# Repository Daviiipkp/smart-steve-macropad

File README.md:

# Smart Steve Commander v1

A custom mechanical macropad designed to control the "Smart Steve" personal automation assistant. It features a rotary encoder for volume/media control, an OLED screen for system status, and 8 mechanical keys for shortcuts.

Designed using KiCad and Fusion 360.

## Features
* **MCU:** Seeed XIAO RP2040
* **Inputs:** 8x MX-Style Mechanical Switches + 1x EC11 Rotary Encoder
* **Display:** 0.91" OLED I2C Display
* **Lighting:** 1x SK6812 (Neopixel) RGB LED for status indication
* **Case:** 3D Printed Sandwich Case

## Project Structure
* `/CAD`: Contains the complete 3D assembly (.STEP)
* `/PCB`: KiCad source files
* `/Firmware`: CircuitPython/KMK placeholder

## Bill of Materials (BOM)

| Component | Quantity | Description |
| :--- | :--- | :--- |
| Seeed XIAO RP2040 | 1 | Microcontroller |
| Cherry MX Style Switch | 8 | Mechanical Keys |
| Keycaps | 8 | 1U Keycaps |
| EC11 Rotary Encoder | 1 | Encoder with Push Button |
| 0.91" OLED Display | 1 | I2C 128x32 Display |
| SK6812 / WS2812B | 1 | RGB LED (5050 package) |
| 1N4148 Diodes | 9 | Through-hole diodes |
| 3D Printed Case | 1 | PLA/PETG |

## Gallery

### 3D Assembly

### PCB Layout

### Schematic

### Case Assembly (Cross Section)

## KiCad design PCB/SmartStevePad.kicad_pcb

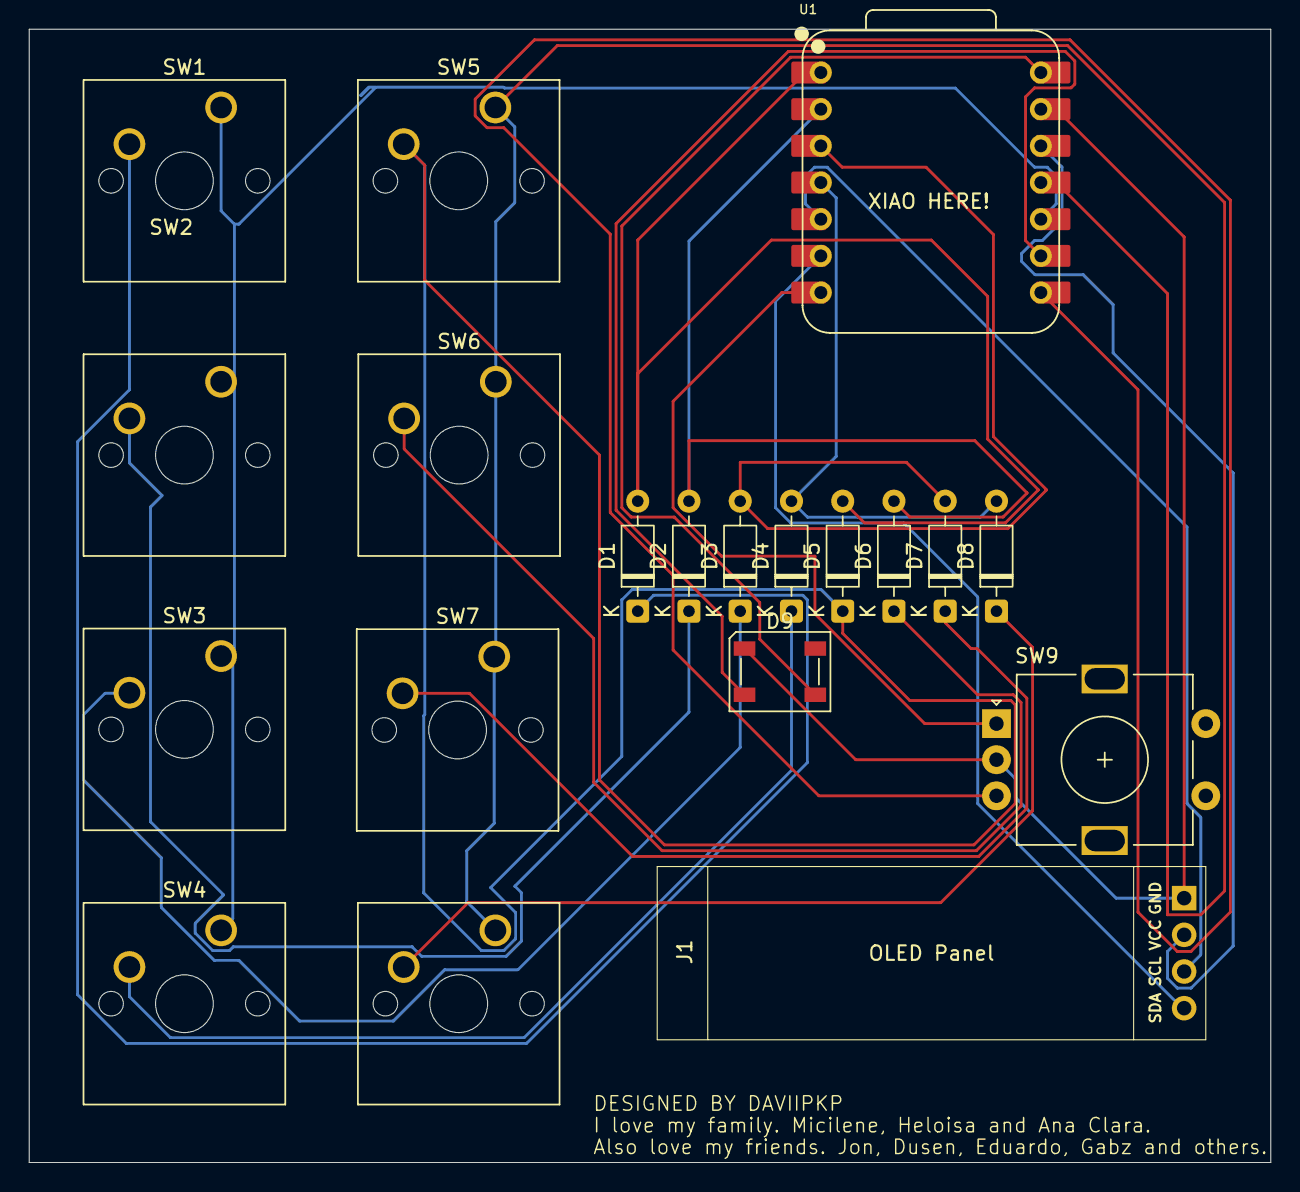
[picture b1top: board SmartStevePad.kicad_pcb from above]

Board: 2 copper layers, 86.0 x 78.5 mm, 20 parts (0 on the bottom side), 22 nets.

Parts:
D1, D2, D3, D4, D5, D6, D7, D8: 1N4148; D_DO-35_SOD27_P7.62mm_Horizontal
D9: SK6812; LED_SK6812_PLCC4_5.0x5.0mm_P3.2mm
J1: Conn_01x04_Socket; SSD1306-0.91-OLED-4pin-128x32
SW1, SW2, SW3, SW4, SW5, SW6, SW7, SW8: SW_Push; SW_Cherry_MX_1.00u_PCB
SW9: RotaryEncoder; RotaryEncoder_Alps_EC11E-Switch_Vertical_H20mm
U1: XIAO-RP2040-DIP

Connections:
unnamed: D1.2 (A), D5.2 (A), U1.1 (GPIO26/ADC0/A0)
unnamed: D1.1 (K), SW1.2
unnamed: D2.2 (A), D6.2 (A), U1.2 (GPIO27/ADC1/A1)
unnamed: D2.1 (K), SW2.2
unnamed: D3.2 (A), D7.2 (A), U1.3 (GPIO28/ADC2/A2)
unnamed: D3.1 (K), SW3.2
unnamed: D4.2 (A), D8.2 (A), U1.4 (GPIO29/ADC3/A3)
unnamed: D4.1 (K), SW4.2
unnamed: D5.1 (K), SW5.2
unnamed: D6.1 (K), SW6.2
unnamed: D7.1 (K), SW7.2
unnamed: D8.1 (K), SW8.2
unnamed: D9.2 (DIN), U1.9 (GPIO2/SCK)
unnamed: D9.3 (VDD), U1.14 (VBUS)
unnamed: D9.1 (VSS), J1.1, SW9.C, U1.13 (GND)
unnamed: J1.2, U1.12 (3V3)
unnamed: J1.3, U1.5 (GPIO6/SDA)
unnamed: J1.4, U1.6 (GPIO7/SCL)
unnamed: SW9.A, U1.7 (GPIO0/TX)
unnamed: SW9.B, U1.8 (GPIO1/RX)
unnamed: SW5.1, SW6.1, SW7.1, SW8.1, U1.11 (GPIO3/MOSI)
unnamed: SW1.1, SW2.1, SW3.1, SW4.1, U1.10 (GPIO4/MISO)

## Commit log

2025-12-15 Files
2025-12-15 Last commit (I expect)
2025-12-16 Update README.md
    Added some new images
